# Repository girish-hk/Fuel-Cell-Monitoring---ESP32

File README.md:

# Fuel Cell DAQ PCB – ESP32-S3

This repository contains the hardware design of a **Fuel Cell Monitoring and Measurement Board** developed in KiCad.  
The board is designed to monitor key electrical parameters of a PEM fuel cell system and interface with an **ESP32-S3** microcontroller.

  ## Project Overview
- Application: Fuel Cell Monitoring & Data Acquisition
- Input Voltage Range: 24V – 45V DC
- Microcontroller: ESP32-S3
- PCB Design Tool: KiCad 8

##  Key Design Features
- **High-side current sensing** for accurate measurement
- **Galvanic isolation** between control and measurement domains
- **Low-noise analog signal conditioning**
- PCB verified using **ERC and DRC checks** in KiCad

##  3D Board View

### Top View

### Bottom View

##  Repository Structure
- `Hardware/` – KiCad schematic and PCB layout files  
- `Libraries/` – Custom symbols and footprints  
- `Production/` – Gerber files and Bill of Materials  
- `Docs/` – Schematic PDF and project documentation  
- `Images/` – 3D rendered views of the PCB  

## Tools Used
- KiCad 8 (Schematic & PCB Design)
- ESP32-S3 platform
- GitHub for version control and documentation

##  Author
**Girish**  
Master’s Student – HS Wismar

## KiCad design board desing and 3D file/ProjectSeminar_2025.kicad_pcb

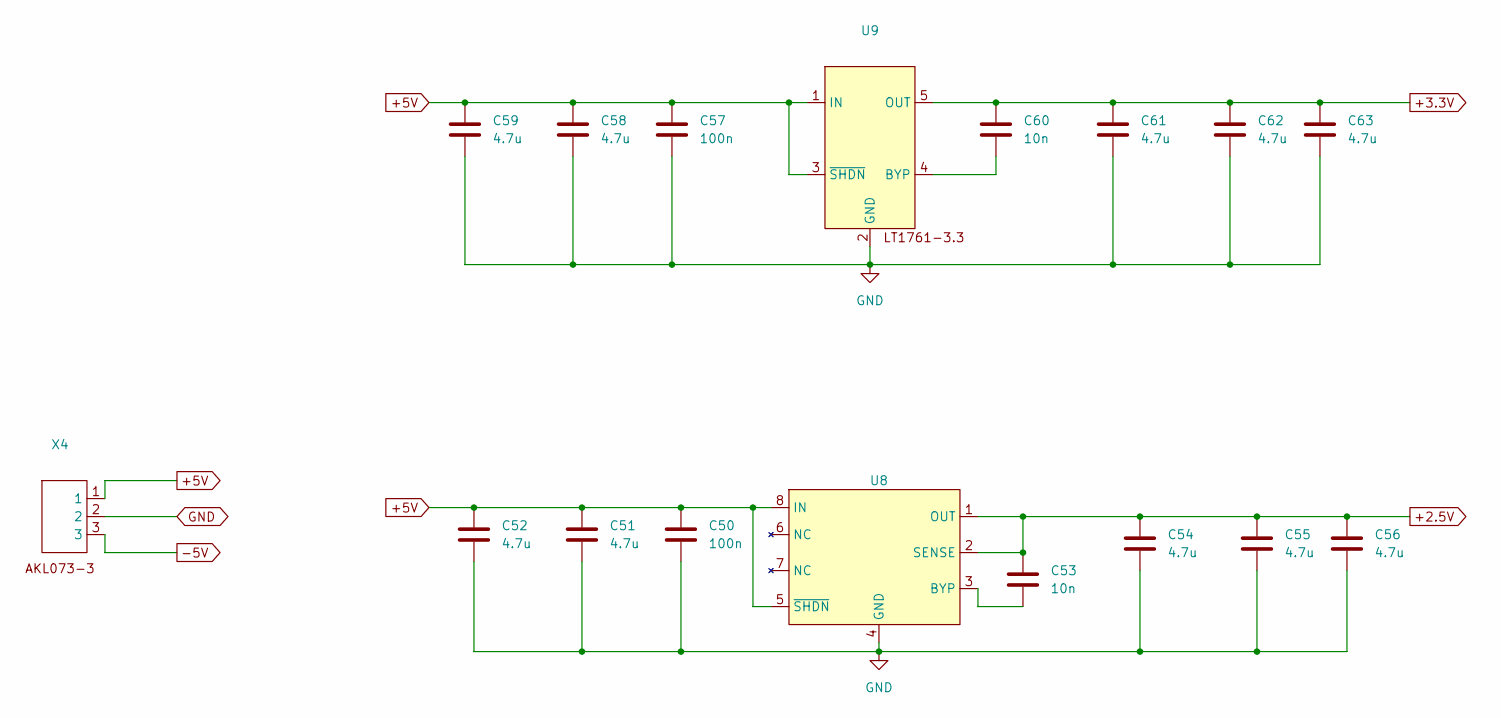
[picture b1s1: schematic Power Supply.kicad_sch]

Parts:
C50, C57: 100n; C_0603_1608Metric_Pad1.08x0.95mm_HandSolder
C51, C52, C54, C55, C56, C58, C59, C61, C62, C63: 4.7u; C_0603_1608Metric_Pad1.08x0.95mm_HandSolder
C53, C60: 10n; C_0603_1608Metric_Pad1.08x0.95mm_HandSolder
U8: LT1762EMS8-2.5
U9: LT1761IS5-3.3
X4: AKL073-3.pretty

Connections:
+2.5V: C53.1, C54.1, C55.1, C56.1, U8.1 (OUT), U8.2 (SENSE); also elsewhere on the board
+3.3V: C60.1, C61.1, C62.1, C63.1, U9.5 (OUT); also elsewhere on the board
+5V: C50.1, C51.1, C52.1, C57.1, C58.1, C59.1, U8.5 (~SHDN), U8.8 (IN), U9.1 (IN), U9.3 (~SHDN), X4.1; also elsewhere on the board
-5V: X4.3; also elsewhere on the board
GND: C50.2, C51.2, C52.2, C54.2, C55.2, C56.2, C57.2, C58.2, C59.2, C61.2, C62.2, C63.2, U8.4 (GND), U9.2 (GND), X4.2; also elsewhere on the board
unnamed: C53.2, U8.3 (BYP)
unnamed: C60.2, U9.4 (BYP)

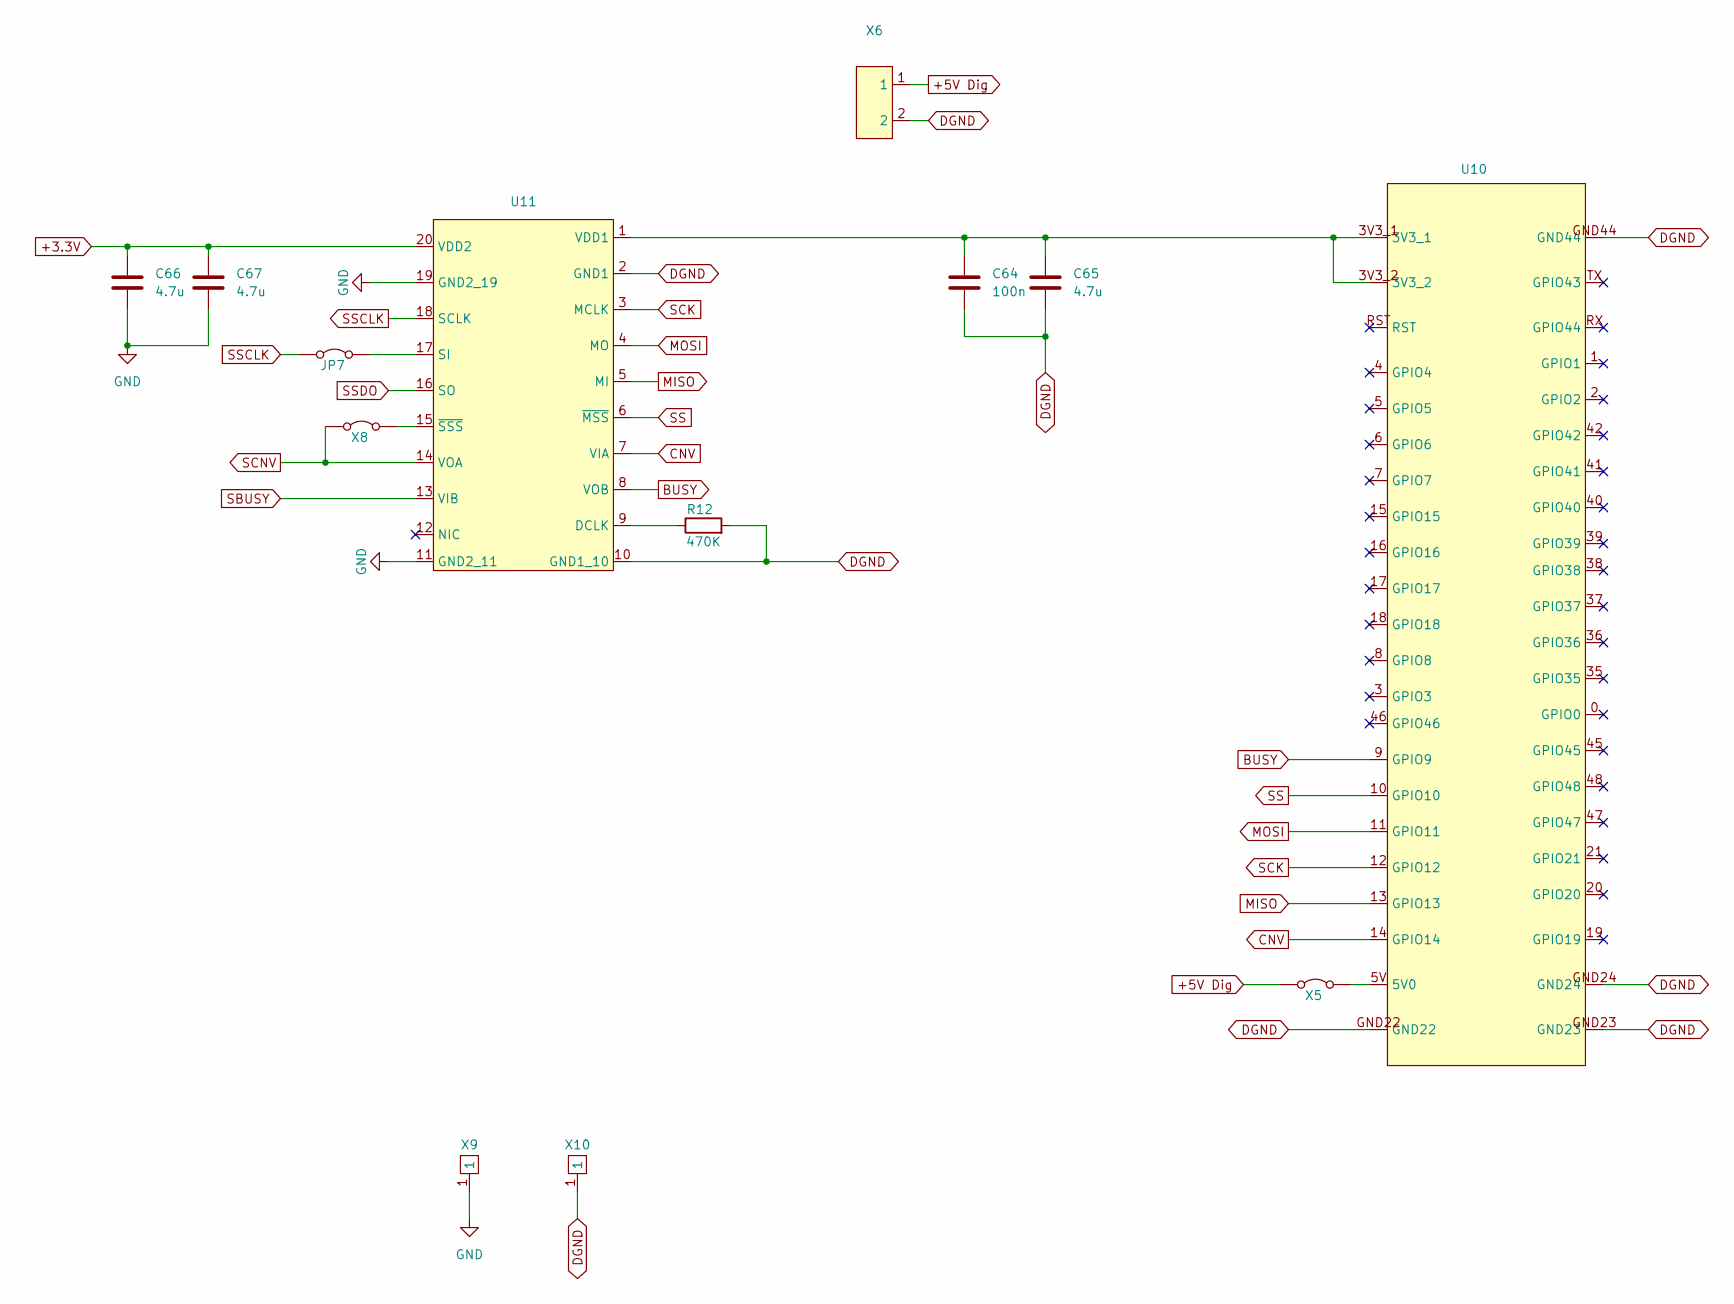
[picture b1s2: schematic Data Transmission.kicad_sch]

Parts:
C64: 100n; C_0603_1608Metric_Pad1.08x0.95mm_HandSolder
C65, C66, C67: 4.7u; C_0603_1608Metric_Pad1.08x0.95mm_HandSolder
JP7: Jumper_2_Bridged; MPE-087-1-002(1)
R12: 470K; R_0402_1005Metric_Pad0.72x0.64mm_HandSolder
U10: ESP32-S3-DevKitC-1N8; ESP32-S3-DevKitC
U11: ADUM4150BRIZ
X5, X8: MPE-087-1-002(1)
X6: AKL072
X9, X10: rtm

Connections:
+3.3V: C66.1, C67.1, U11.20 (VDD2); also elsewhere on the board
+5V Dig: X5.1 (A), X6.1
BUSY: U10.9 (GPIO9), U11.8 (VOB)
CNV: U10.14 (GPIO14), U11.7 (VIA)
DGND: C64.2, C65.2, R12.2, U10.GND22, U10.GND23, U10.GND24, U10.GND44, U11.2 (GND1), U11.10 (GND1_10), X6.2, X10.1
GND: C66.2, C67.2, U11.11 (GND2_11), U11.19 (GND2_19), X9.1; also elsewhere on the board
MISO: U10.13 (GPIO13), U11.5 (MI)
MOSI: U10.11 (GPIO11), U11.4 (MO)
unnamed: JP7.2 (B), U11.17 (SI)
unnamed: U10.5V (5V0), X5.2 (B)
unnamed: R12.1, U11.9 (DCLK)
unnamed: C64.1, C65.1, U10.3V3_1, U10.3V3_2, U11.1 (VDD1)
unnamed: U11.15 (~SSS), X8.2 (B)
SBUSY: U11.13 (VIB); also elsewhere on the board
SCK: U10.12 (GPIO12), U11.3 (MCLK); also elsewhere on the board
SCNV: U11.14 (VOA), X8.1 (A); also elsewhere on the board
SS: U10.10 (GPIO10), U11.6 (~MSS)
SSCLK: JP7.1 (A), U11.18 (SCLK)
SSDO: U11.16 (SO); also elsewhere on the board

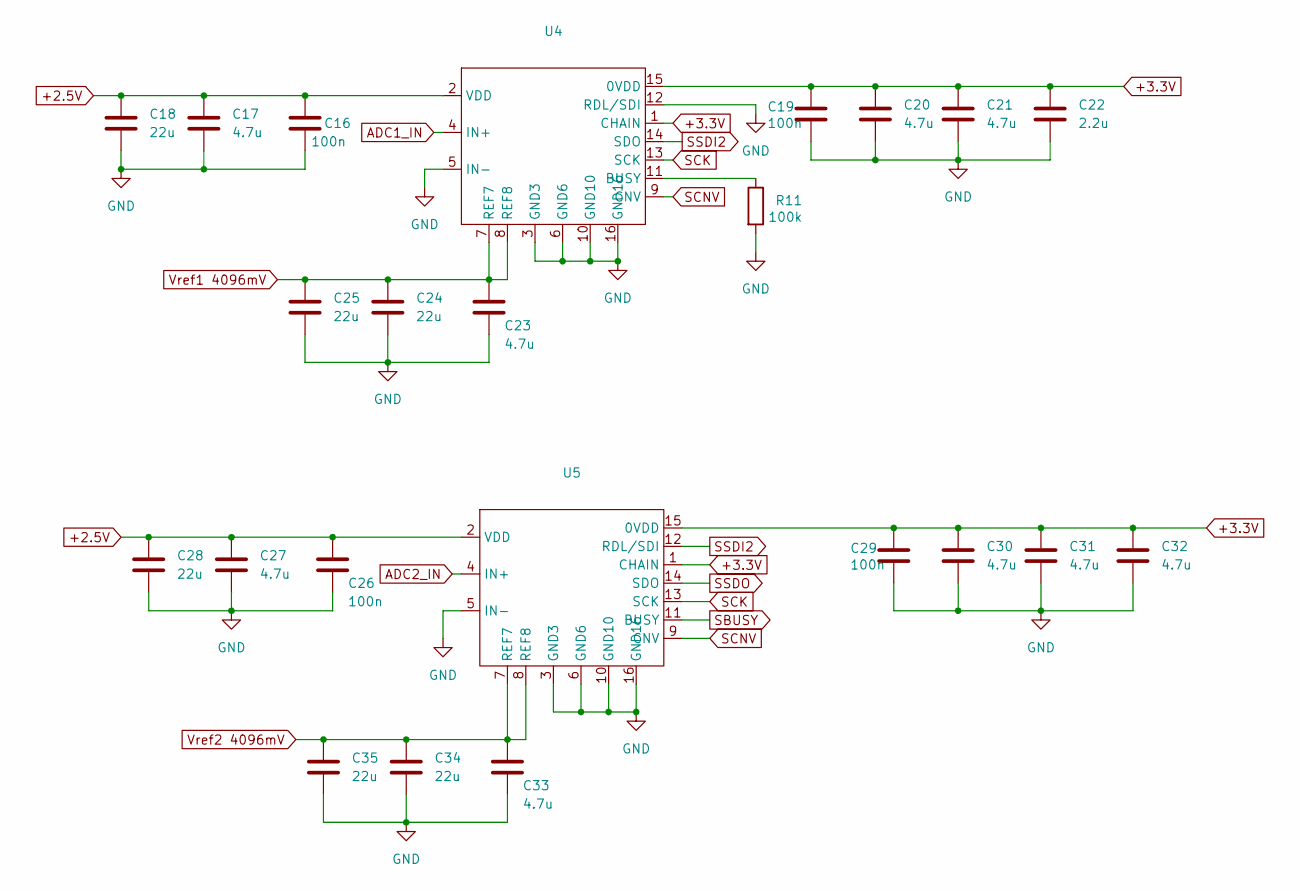
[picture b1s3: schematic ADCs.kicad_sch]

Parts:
C16, C19, C26, C29: 100n; C_0603_1608Metric_Pad1.08x0.95mm_HandSolder
C17, C20, C21, C23, C27, C30, C31, C32, C33: 4.7u; C_0603_1608Metric_Pad1.08x0.95mm_HandSolder
C18, C24, C25, C28, C34, C35: 22u; C_0805_2012Metric_Pad1.18x1.45mm_HandSolder
C22: 2.2u; C_0603_1608Metric_Pad1.08x0.95mm_HandSolder
R11: 100k; R_0603_1608Metric_Pad0.98x0.95mm_HandSolder
U4, U5: LTC2368IMS-16

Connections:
+2.5V: C16.1, C17.1, C18.1, C26.1, C27.1, C28.1, U4.2 (VDD), U5.2 (VDD); also elsewhere on the board
+3.3V: C19.1, C20.1, C21.1, C22.1, C29.1, C30.1, C31.1, C32.1, U4.1 (CHAIN), U4.15 (0VDD), U5.1 (CHAIN), U5.15 (0VDD); also elsewhere on the board
ADC1_IN: U4.4 (IN+); also elsewhere on the board
ADC2_IN: U5.4 (IN+); also elsewhere on the board
GND: C16.2, C17.2, C18.2, C19.2, C20.2, C21.2, C22.2, C23.2, C24.2, C25.2, C26.2, C27.2, C28.2, C29.2, C30.2, C31.2, C32.2, C33.2, C34.2, C35.2, R11.2, U4.3 (GND3), U4.5 (IN-), U4.6 (GND6), U4.10 (GND10), U4.12 (RDL/SDI), U4.16 (GND16), U5.3 (GND3), U5.5 (IN-), U5.6 (GND6), U5.10 (GND10), U5.16 (GND16); also elsewhere on the board
unnamed: R11.1, U4.11 (BUSY)
SBUSY: U5.11 (BUSY); also elsewhere on the board
SCK: U4.13 (SCK), U5.13 (SCK); also elsewhere on the board
SCNV: U4.9 (CNV), U5.9 (CNV); also elsewhere on the board
SSDI2: U4.14 (SDO), U5.12 (RDL/SDI)
SSDO: U5.14 (SDO); also elsewhere on the board
Vref1 4096mV: C23.1, C24.1, C25.1, U4.7 (REF7), U4.8 (REF8); also elsewhere on the board
Vref2 4096mV: C33.1, C34.1, C35.1, U5.7 (REF7), U5.8 (REF8); also elsewhere on the board

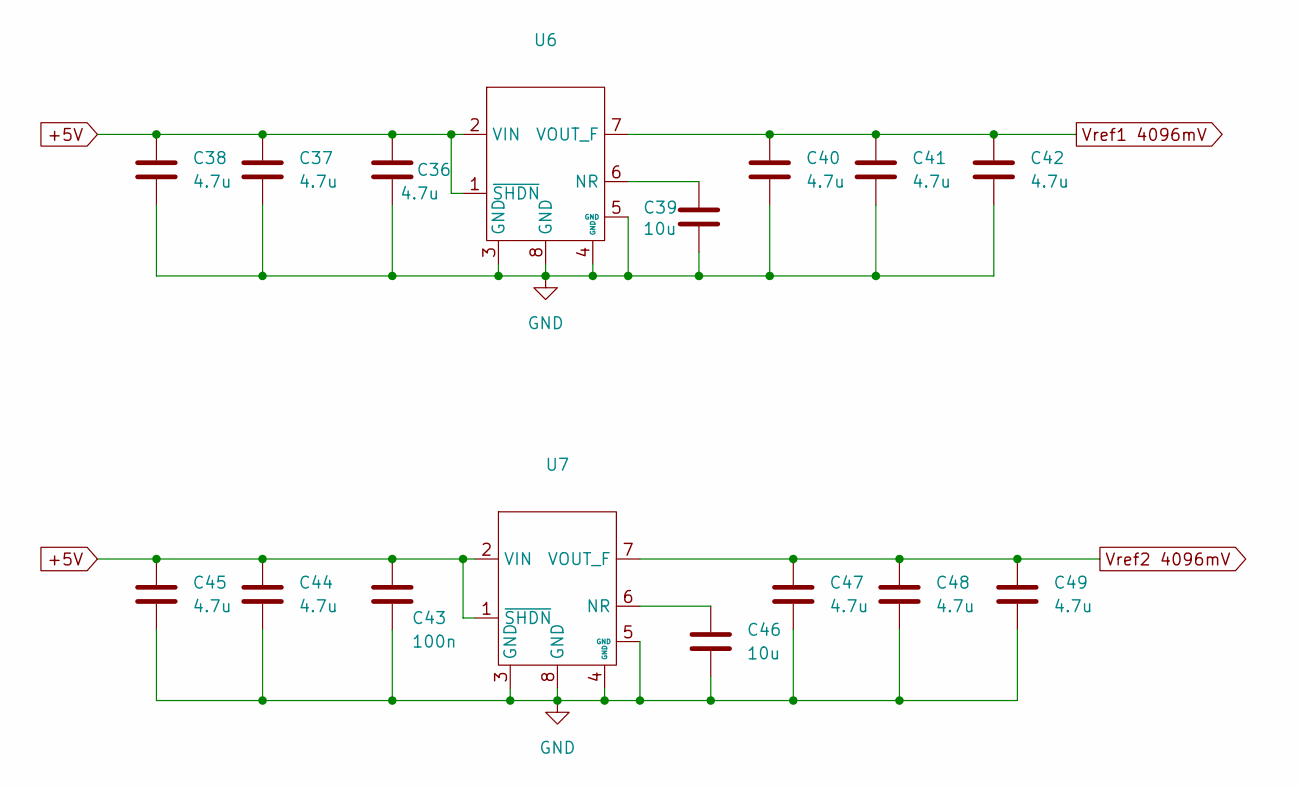
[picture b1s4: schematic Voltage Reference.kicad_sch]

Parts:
C36, C37, C38, C40, C41, C42, C44, C45, C47, C48, C49: 4.7u; C_0603_1608Metric_Pad1.08x0.95mm_HandSolder
C39, C46: 10u; C_0603_1608Metric_Pad1.08x0.95mm_HandSolder
C43: 100n; C_0603_1608Metric_Pad1.08x0.95mm_HandSolder
U6, U7: LTC6655LNBHMS8

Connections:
+5V: C36.1, C37.1, C38.1, C43.1, C44.1, C45.1, U6.1 (~SHDN), U6.2 (VIN), U7.1 (~SHDN), U7.2 (VIN); also elsewhere on the board
GND: C36.2, C37.2, C38.2, C39.2, C40.2, C41.2, C42.2, C43.2, C44.2, C45.2, C46.2, C47.2, C48.2, C49.2, U6.3 (GND), U6.4 (GND), U6.5 (GND), U6.8 (GND), U7.3 (GND), U7.4 (GND), U7.5 (GND), U7.8 (GND); also elsewhere on the board
unnamed: C39.1, U6.6 (NR)
unnamed: C46.1, U7.6 (NR)
Vref1 4096mV: C40.1, C41.1, C42.1, U6.7 (VOUT_F); also elsewhere on the board
Vref2 4096mV: C47.1, C48.1, C49.1, U7.7 (VOUT_F); also elsewhere on the board

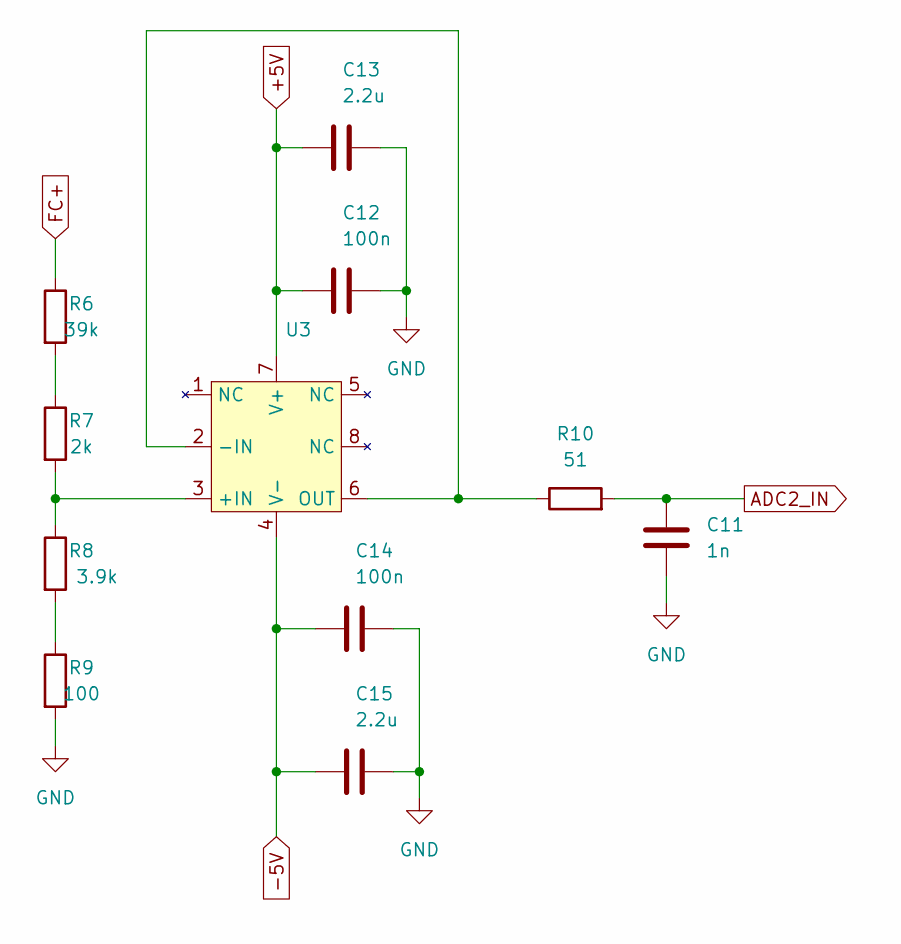
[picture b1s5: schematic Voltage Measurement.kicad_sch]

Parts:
C11: 1n; C_0603_1608Metric_Pad1.08x0.95mm_HandSolder
C12, C14: 100n; C_0603_1608Metric_Pad1.08x0.95mm_HandSolder
C13, C15: 2.2u; C_0603_1608Metric_Pad1.08x0.95mm_HandSolder
R6: 39k; R_0603_1608Metric_Pad0.98x0.95mm_HandSolder
R7: 2k; R_0603_1608Metric_Pad0.98x0.95mm_HandSolder
R8: 3.9k; R_0603_1608Metric_Pad0.98x0.95mm_HandSolder
R9: 100; R_0603_1608Metric_Pad0.98x0.95mm_HandSolder
R10: 51; R_0603_1608Metric_Pad0.98x0.95mm_HandSolder
U3: LT6202IS8

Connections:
+5V: C12.2, C13.2, U3.7 (V+); also elsewhere on the board
-5V: C14.2, C15.2, U3.4 (V-); also elsewhere on the board
ADC2_IN: C11.1, R10.2; also elsewhere on the board
FC+: R6.1
GND: C11.2, C12.1, C13.1, C14.1, C15.1, R9.2; also elsewhere on the board
unnamed: R6.2, R7.1
unnamed: R8.2, R9.1
unnamed: R7.2, R8.1, U3.3 (+IN)
unnamed: R10.1, U3.2 (-IN), U3.6 (OUT)

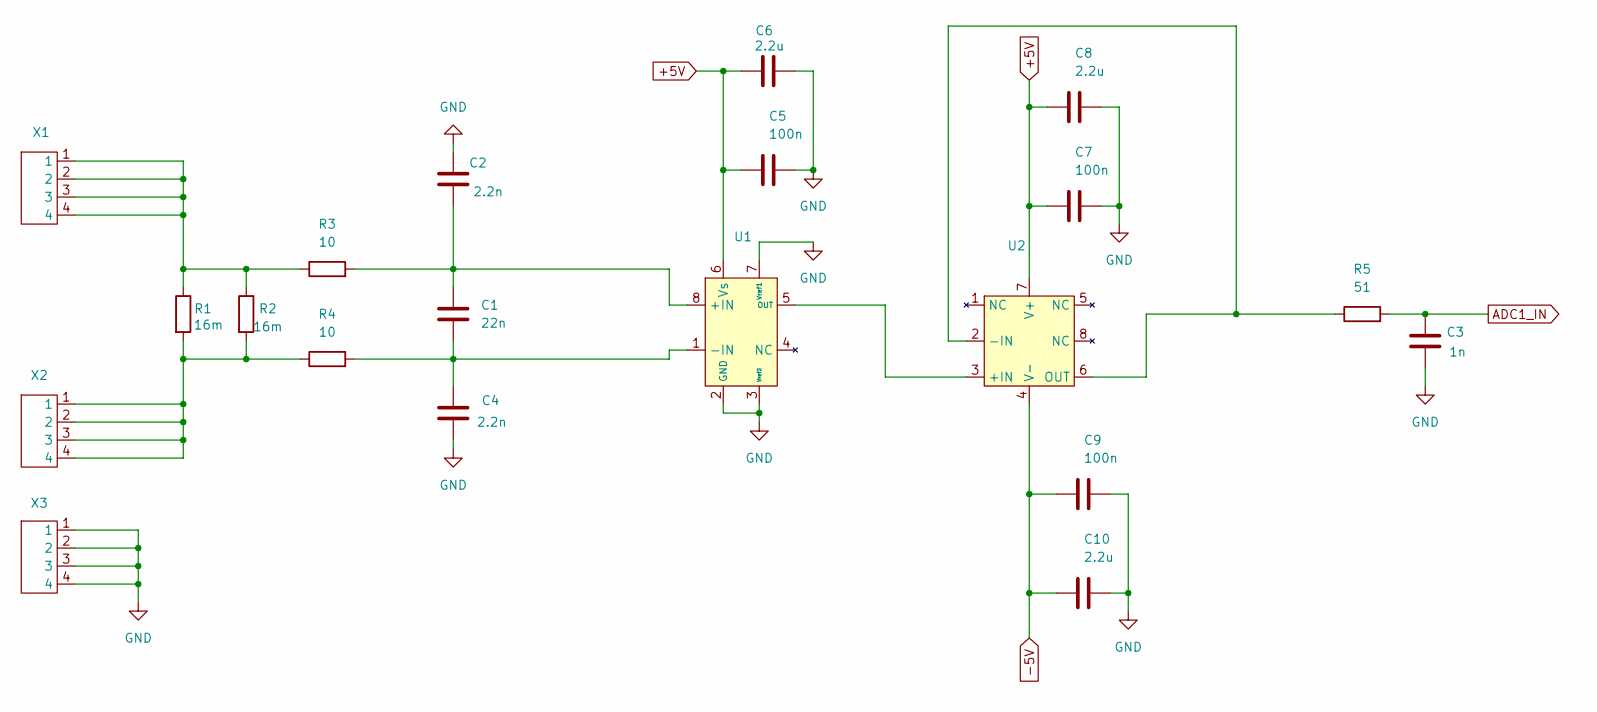
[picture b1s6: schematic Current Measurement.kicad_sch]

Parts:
C1: 22n; C_0603_1608Metric_Pad1.08x0.95mm_HandSolder
C2, C4: 2.2n; C_0603_1608Metric_Pad1.08x0.95mm_HandSolder
C3: 1n; C_0603_1608Metric_Pad1.08x0.95mm_HandSolder
C5, C7, C9: 100n; C_0603_1608Metric_Pad1.08x0.95mm_HandSolder
C6, C8, C10: 2.2u; C_0603_1608Metric_Pad1.08x0.95mm_HandSolder
R1, R2: 16m; R_2512_6332Metric_Pad1.40x3.35mm_HandSolder
R3, R4: 10; R_0603_1608Metric_Pad0.98x0.95mm_HandSolder
R5: 51; R_0603_1608Metric_Pad0.98x0.95mm_HandSolder
U1: AD8410ABWRZ
U2: LT6202IS8
X1, X2, X3: Connectors

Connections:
+5V: C5.2, C6.2, C7.2, C8.2, U1.6 (Vs), U2.7 (V+); also elsewhere on the board
-5V: C9.2, C10.2, U2.4 (V-); also elsewhere on the board
ADC1_IN: C3.2, R5.2; also elsewhere on the board
GND: C2.2, C3.1, C4.1, C5.1, C6.1, C7.1, C8.1, C9.1, C10.1, U1.2 (GND), U1.3 (Vref2), U1.7 (Vref1), X3.1, X3.2, X3.3, X3.4; also elsewhere on the board
unnamed: R1.1, R2.1, R3.1, X1.1, X1.2, X1.3, X1.4
unnamed: R1.2, R2.2, R4.1, X2.1, X2.2, X2.3, X2.4
unnamed: C1.1, C2.1, R3.2, U1.8 (+IN)
unnamed: C1.2, C4.2, R4.2, U1.1 (-IN)
unnamed: U1.5 (OUT), U2.3 (+IN)
unnamed: R5.1, U2.2 (-IN), U2.6 (OUT)

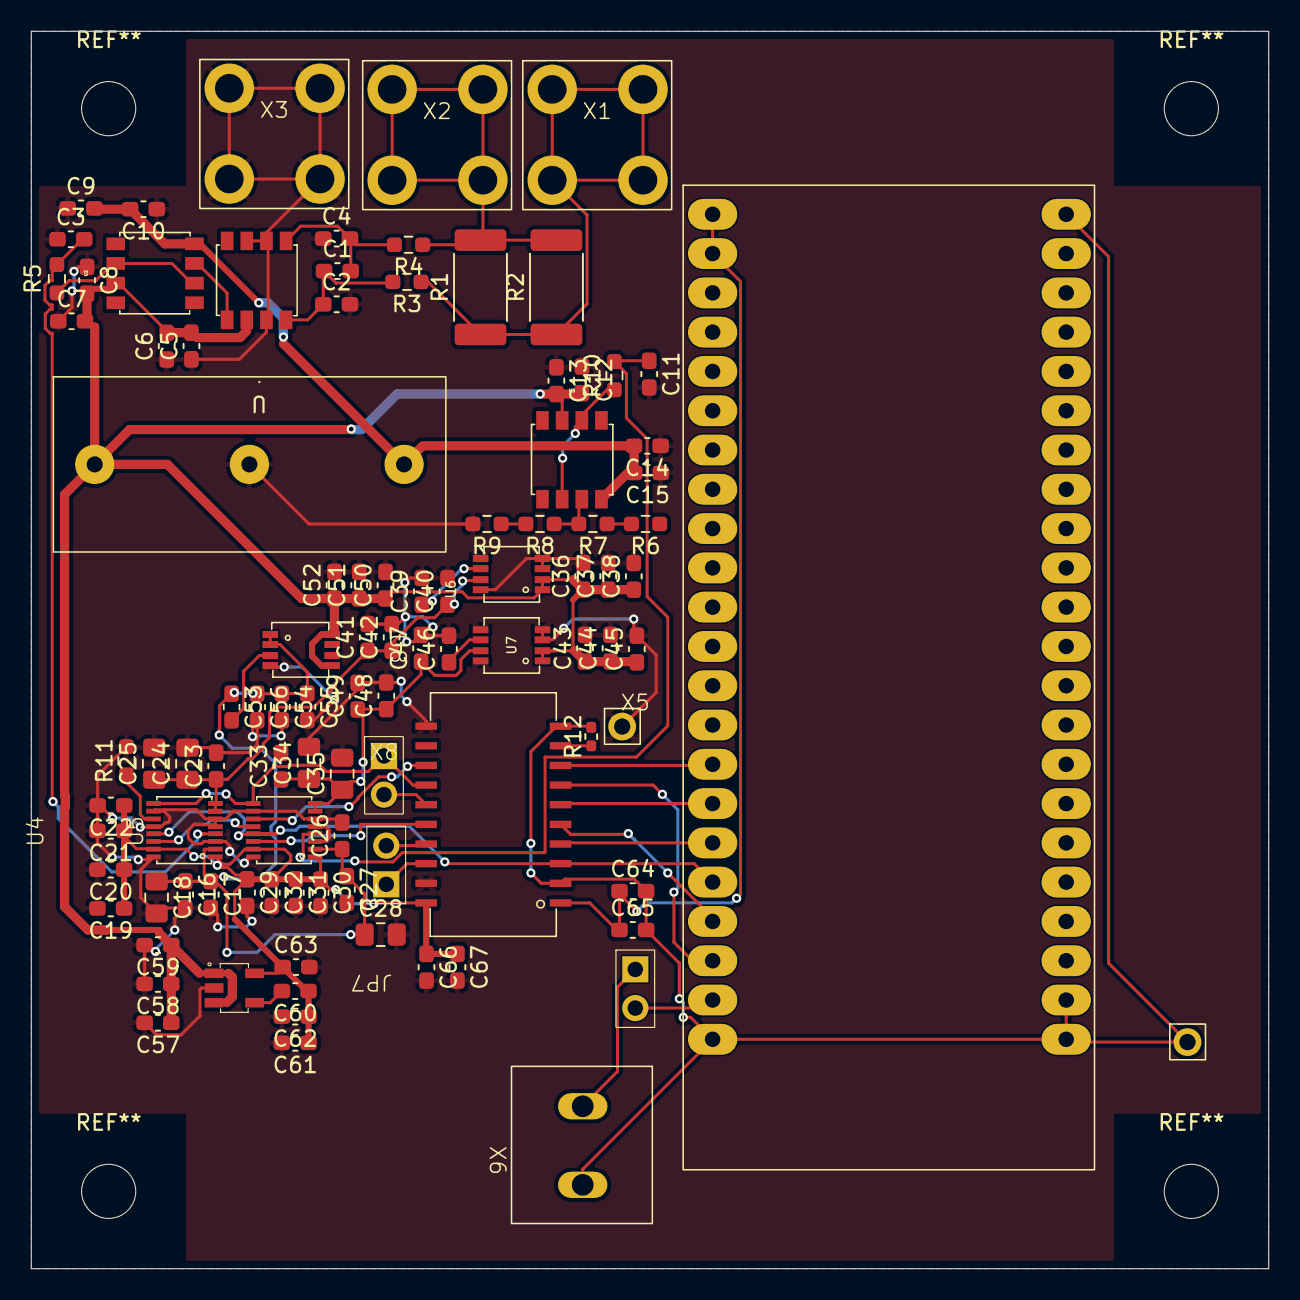
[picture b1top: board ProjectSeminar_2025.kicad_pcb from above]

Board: 2 copper layers, 80.0 x 80.0 mm, 100 parts (0 on the bottom side), 42 nets.

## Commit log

2026-02-09 Fix formatting of Project Overview section in README
2026-02-09 Update README to remove Master's project mention
    Removed project affiliation details from README.
